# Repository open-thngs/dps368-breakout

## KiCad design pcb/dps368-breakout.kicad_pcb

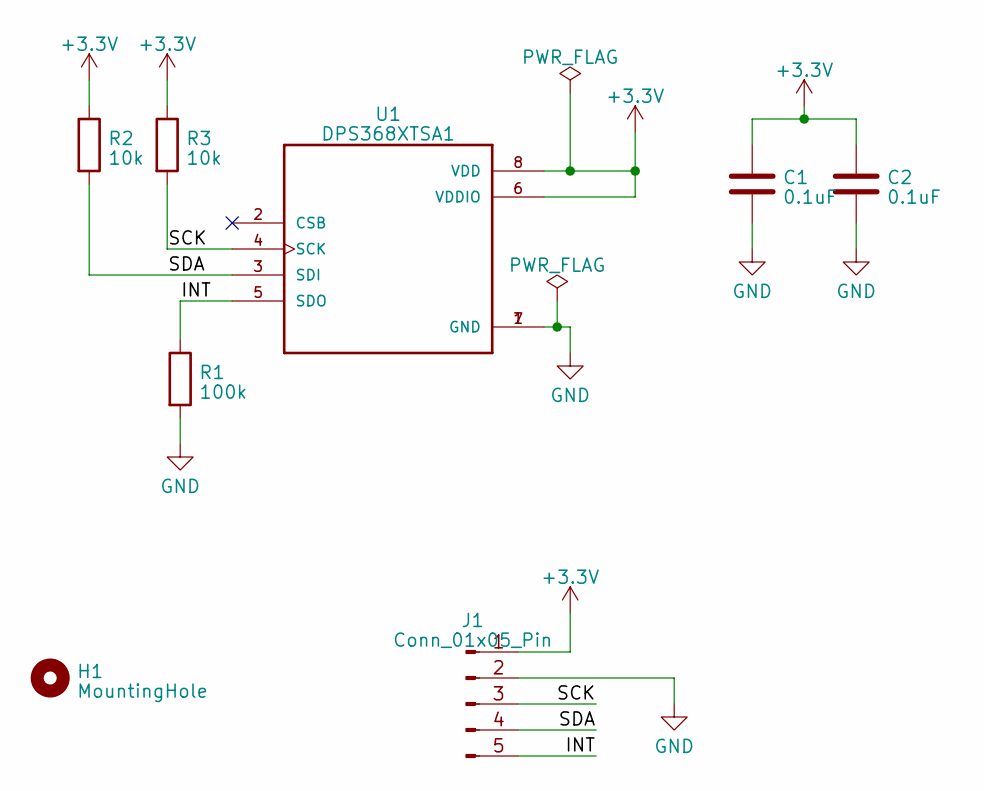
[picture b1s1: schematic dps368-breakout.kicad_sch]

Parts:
C1, C2: 0.1uF; C_0603_1608Metric
H1: MountingHole; MountingHole_2.5mm_Pad_Via
J1: Conn_01x05_Pin; PinSocket_1x05_P2.54mm_Vertical
R1: 100k; R_0603_1608Metric
R2, R3: 10k; R_0603_1608Metric
U1: DPS368XTSA1; XDCR_DPS368XTSA1

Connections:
+3.3V: C1.1, C2.1, J1.1, R2.1, R3.1, U1.6 (VDDIO), U1.8 (VDD)
/INT: J1.5, R1.1, U1.5 (SDO)
/SCK: J1.3, R3.2, U1.4 (SCK)
/SDA: J1.4, R2.2, U1.3 (SDI)
GND: C1.2, C2.2, J1.2, R1.2, U1.1 (GND), U1.7 (GND)

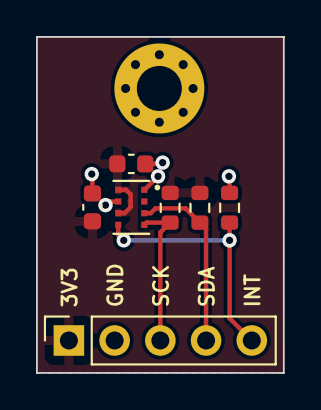
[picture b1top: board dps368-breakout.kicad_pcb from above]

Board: 2 copper layers, 13.7 x 18.7 mm, 8 parts (0 on the bottom side), 5 nets.

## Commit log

2023-04-12 Added font to repo
2023-04-12 Added font license
2023-04-12 Changed license informations for the font
2023-04-12 Named the license file correctly
2023-04-12 Added license OFL-1.0 text
2023-04-12 Removed broken property
2023-04-12 Modified DRC rules
2023-06-08 Added mounting hole
2023-06-15 Update kibot.yml with Quick Start solution
